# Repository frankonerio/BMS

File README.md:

# Battery Management System (BMS) Project

## Overview
This project has been developed using the following software and libraries:

- **ROS 2**
- **libmodbus** - [Official Website](https://libmodbus.org/)
- **STM32CubeIDE v1.15.1**
- **Segger SystemView Software (PC)** - [Download](https://www.segger.com/products/development-tools/systemview/)
- **Segger SystemView Target Source Files v3.20 (Target Board)**
- **FreeRTOS** - Real-time operating system
- **Wiznet W5500 ioLibrary_BSD** - [Documentation](https://docs.wiznet.io/Product/iEthernet/W5500/driver)

**Author:** fokonkwo@mail.upb.de  
**Date:** 15.01.2025  

---

## 1. BMS Directory Structure

```
├── bms
│   ├── bms.ioc
│   ├── Core
│   │   ├── Inc
│   │   │   ├── BQ769x2Header.h
│   │   │   ├── modbus.h
│   │   │   ├── soc.h
│   │   │   ├── spi.h
│   │   │   ├── FreeRTOSConfig.h    // FreeRTOS configuration or customization file
│   │   ├── Src
│   │   │   ├── main.c
│   │   │   ├── modbus.c    // Modbus battery management system --> host robot communication functions
│   │   │   ├── soc.c    // State estimation functions Coulomb counting and extended Kalman filter functions
│   │   │   ├── utils.c
│   │   ├── Startup
│   │   │   └── startup_stm32f446retx.s
│   ├── Drivers
│   │   ├── CMSIS
│   │   ├── STM32F4xx_HAL_Driver
│   ├── ThirdParty
│   │   ├── FreeRTOS-Kernel
│   │   ├── SEGGER    // For task execution trace capture and debugging real time systems
├── bms_gui
│   ├── include
│   │   └── bms_gui
│   │       ├── mainwindow.h
│   │       └── ros2comm.h  
│   ├── src
│   │   ├── main.cpp
│   │   ├── mainwindow.cpp
│   │   └── ros2comm.cpp    / ROS 2 host node for bms--> host communication and gui interface update
├── FreeRTOS11_with_SystemView.pdf
├── qt_gui
│   ├── main.cpp
│   ├── mainwindow.cpp
│   ├── mainwindow.h
│   ├── mainwindow.ui
└── README.md
```

---

## 2. Getting Started

1. Clone or download and unzip the folder.
2. Run `git submodule init && git submodule update` to initialize and update the FreeRTOS submodule.
3. Open **STM32CubeIDE** and import the project into your workspace.
4. Build the project.
   - If the build fails, ensure all paths are correctly set up.
   - Check project configurations and resolve any missing dependencies.

---

## 3. Integrating FreeRTOS

- Manually added FreeRTOS as a submodule.
- To include FreeRTOS in the STM32CubeIDE project:
  - Create a `ThirdParty` directory and include the FreeRTOS kernel.
  - Include these compiler paths:
    ```
    "${workspace_loc:/${ProjName}/ThirdParty/FreeRTOS-Kernel/include}"
    "${workspace_loc:/${ProjName}/ThirdParty/FreeRTOS-Kernel/portable/GCC/ARM_CM4F}"
    ```
- Ensure `sysmem.c` is **excluded** from the build.

---

## 4. Integrating SEGGER SystemView

- Download **Segger SystemView** for PC and target source files.
- Extract source files into `ThirdParty/SEGGER`.
- Modify **FreeRTOSConfig.h** to include:
  ```c
  #include "SEGGER_SYSVIEW_FreeRTOS.h"
  #define INCLUDE_xTaskGetIdleTaskHandle 1
  #define INCLUDE_pxTaskGetStackStart 1
  ```
- Configure SystemView buffer size and enable **DWT_CYCCNT** register for timestamping.
- Include these compiler paths:
  ```
  "${workspace_loc:/${ProjName}/ThirdParty/SEGGER/Config}"
  "${workspace_loc:/${ProjName}/ThirdParty/SEGGER/SEGGER}"
  "${workspace_loc:/${ProjName}/ThirdParty/SEGGER/OS}"
  ```

---

## 5. Integrating W5500 Ethernet Library

- Download and include the **Wiznet W5500 ioLibrary**.
- Edit `wizchip_conf.h`:
  ```c
  #define _WIZCHIP_ W5500
  ```

---

## 6. ROS 2 Host Node and BMS GUI

- **Build the ROS 2 node** using `colcon build`.
- To modify the GUI:
  - Open `qt_gui` in **Qt Creator**.
  - Edit `mainwindow.ui` as needed.
  - Rebuild the ROS 2 node.

---
## 7. Hardware

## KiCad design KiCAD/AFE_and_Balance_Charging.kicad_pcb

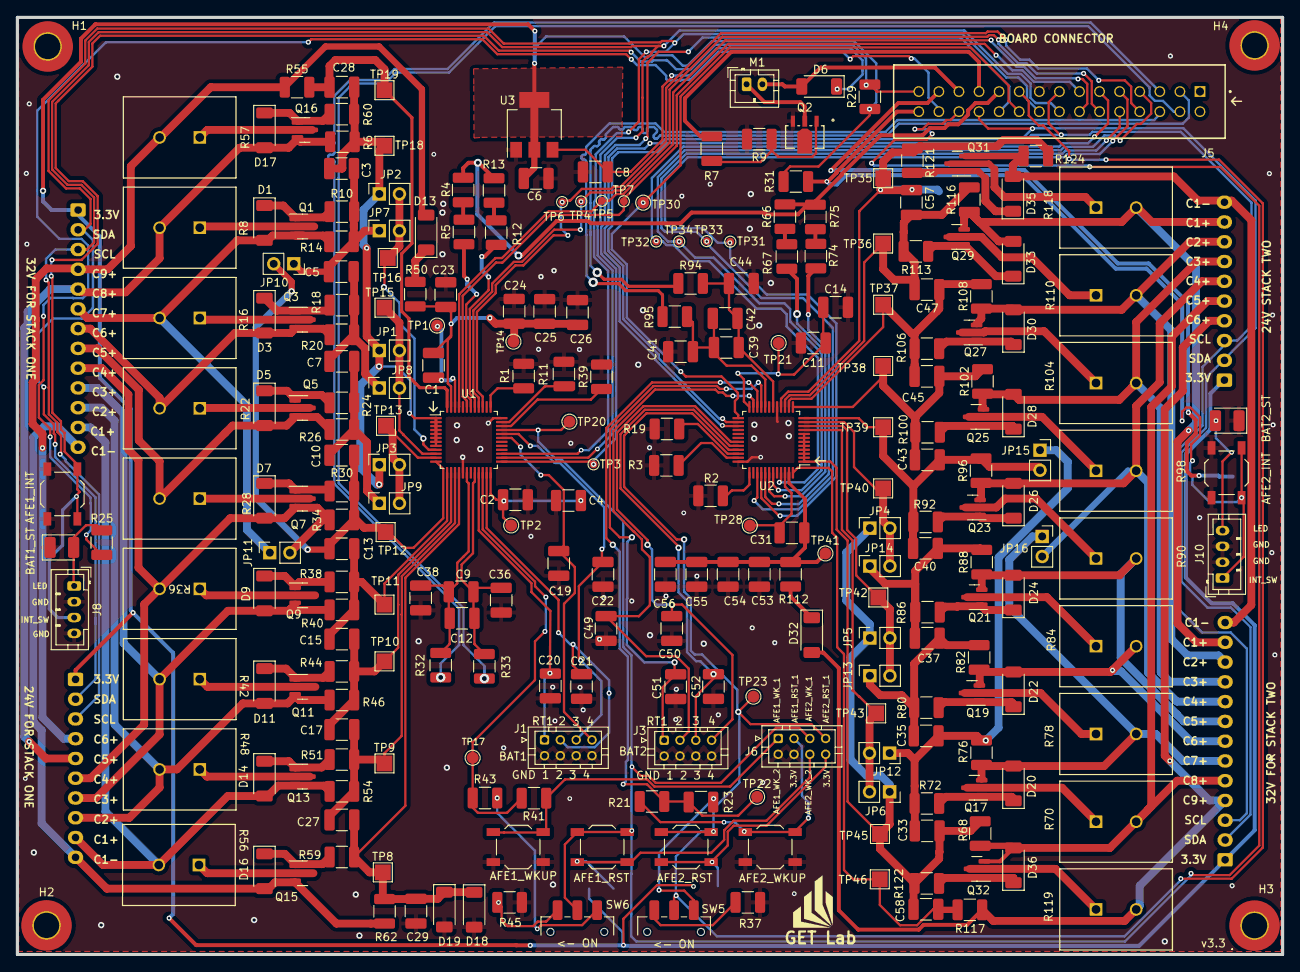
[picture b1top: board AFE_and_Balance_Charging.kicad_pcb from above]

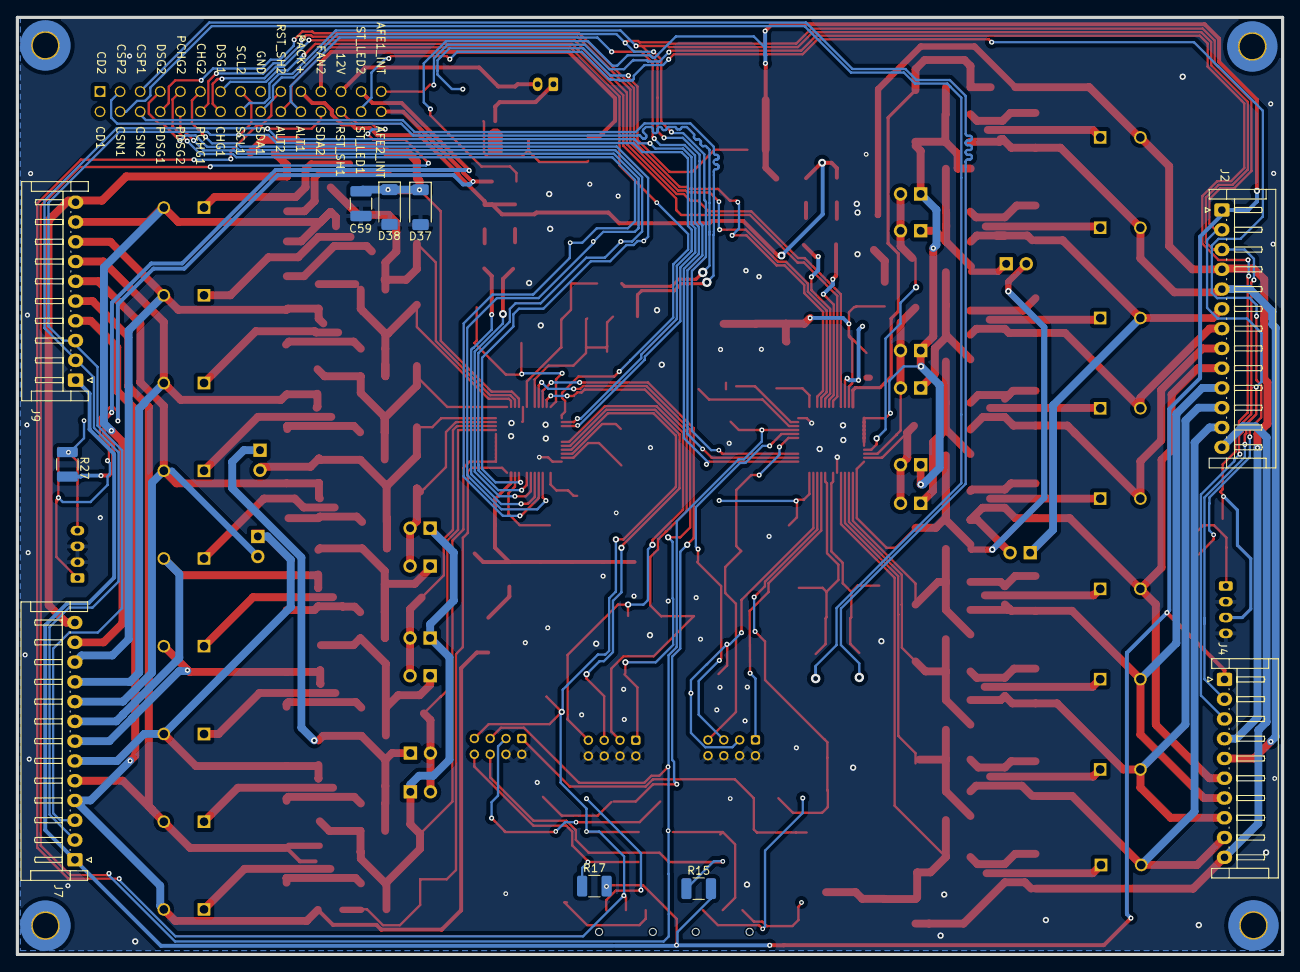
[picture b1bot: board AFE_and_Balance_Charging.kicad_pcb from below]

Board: 2 copper layers, 160.0 x 118.5 mm, 270 parts (10 on the bottom side), 160 nets.

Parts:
C1, C23, C24, C25, C31, C53, C54, C55: 1µF; C_1210_3225Metric_Pad1.33x2.70mm_HandSolder
C2, C11: 2.2µF; C_1210_3225Metric_Pad1.33x2.70mm_HandSolder
C3, C5, C7, C10, C13, C15, C17, C27, C28, C29, C33, C35, C37, C40, C43, C45, C47, C57, C58, C59: 220nF; C_1210_3225Metric_Pad1.33x2.70mm_HandSolder
C4, C14: 0.1uF; C_1210_3225Metric_Pad1.33x2.70mm_HandSolder
C6, C8: 47µF; C_1210_3225Metric_Pad1.33x2.70mm_HandSolder
C9, C19, C20, C21, C22, C26, C39, C49, C50, C51, C52, C56: 100pF; C_1210_3225Metric_Pad1.33x2.70mm_HandSolder
C12, C36, C38, C41, C42, C44: 100nF; C_1210_3225Metric_Pad1.33x2.70mm_HandSolder
D1, D3, D5, D7, D9, D11, D14, D16, D17, D20, D22, D24, D26, D28, D30, D33, D35, D36: 15V; D_SOD-128
D2: YELLOW_LED; LED_1210_3225Metric_Pad1.42x2.65mm_HandSolder
D4: BLUE_LED; LED_1210_3225Metric_Pad1.42x2.65mm_HandSolder
D6, D13, D18, D32, D37: 100V; D_SOD-128
D19, D38: 3.6V; D_SOD-128
H1, H2, H3, H4: MountingHole; MountingHole_3.2mm_M3_Pad_TopBottom
J1, J3: Conn_02x04_Counter_Clockwise; JST_PHD_B8B-PHDSS_2x04_P2.00mm_Vertical
J2, J7: Conn_01x13_Pin; JST_EH_S13B-EH_1x13_P2.50mm_Horizontal
J4, J9: Conn_01x09_Pin; JST_EH_S10B-EH_1x10_P2.50mm_Horizontal
J5: TSS-115-02-L-D; SAMTEC_TSS-115-02-L-D
J6: Conn_02x04_Top_Bottom; JST_PHD_B8B-PHDSS_2x04_P2.00mm_Vertical
J8, J10: Conn_02x02_Top_Bottom; JST_PH_B4B-PH-K_1x04_P2.00mm_Vertical
JP1, JP2, JP3, JP4, JP5, JP6, JP7, JP8, JP9, JP10, JP11, JP12, JP13, JP14, JP15, JP16: Jumper_2_Bridged; PinSocket_1x02_P2.54mm_Vertical
M1: Fan; JST_PH_B2B-PH-K_1x02_P2.00mm_Vertical
Q1, Q3, Q5, Q7, Q9, Q11, Q13, Q15, Q16, Q17, Q19, Q21, Q23, Q25, Q27, Q29, Q31, Q32: AO3416; SOT-23
Q2: FCX495TA; FCX493TA_DIO
R1, R2, R3, R11, R15, R17, R19, R29, R31, R39: 100k; R_1210_3225Metric_Pad1.30x2.65mm_HandSolder
R4, R5, R12, R13, R66, R67, R74, R75: 5.1k; R_1210_3225Metric_Pad1.30x2.65mm_HandSolder
R6, R14, R20, R26, R32, R33, R34, R40, R46, R50, R54, R62, R68, R76, R82, R88, R94, R95, R96, R102, R108, R112, R116, R124: 100; R_1210_3225Metric_Pad1.30x2.65mm_HandSolder
R7, R10, R18, R24, R30, R38, R44, R51, R59, R60, R72, R80, R86, R92, R100, R106, R113, R121, R122: 1k; R_1210_3225Metric_Pad1.30x2.65mm_HandSolder
R8, R16, R22, R28, R36, R42, R48, R56, R57, R70, R78, R84, R90, R98, R104, R110, R118, R119: 4.7; RES_SQM500_YAG
R9, R21, R23, R37, R41, R43, R45: 10k; R_1210_3225Metric_Pad1.30x2.65mm_HandSolder
R25, R27: 4.7K; R_1210_3225Metric_Pad1.30x2.65mm_HandSolder
R55, R117: 20; R_1210_3225Metric_Pad1.30x2.65mm_HandSolder
SW1: Interrupt 2; SW_SPST_TL3342
SW2, SW4, SW7, SW8: Wake_up; SW_SPST_TL3342
SW3: Interrupt 1; SW_SPST_TL3342
SW5, SW6: SHTD; SW_SPDT_CK_JS102011SAQN
TP1, TP2, TP14, TP17, TP20, TP21, TP22, TP23, TP28, TP30, TP41: TestPoint; TestPoint_Pad_D1.5mm
TP3, TP4, TP5, TP6, TP7, TP31, TP32, TP33, TP34: TestPoint; TestPoint_Pad_D1.0mm
TP8, TP9, TP10, TP11, TP12, TP13, TP15, TP16, TP18, TP19, TP35, TP36, TP37, TP38, TP39, TP40, TP42, TP43, TP45, TP46: TestPoint; TestPoint_Pad_2.0x2.0mm
U1, U2: BQ76952PFBR; TQFP-48_7x7mm_P0.5mm
U3: AMS1117-3.3; SOT-223-3_TabPin2

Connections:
+3.3V: C6.1, J2.1, J4.1, J7.1, J9.1, R15.2, R17.2, R29.1, R31.1, U3.2 (VO)
+12V: D6.2 (A), J5.25, M1.2 (-)
/AFE1_INT_A: J5.29, J8.3, R29.2, SW3.1
/AFE1_RST_1: J5.26, J6.5, SW6.2 (B), SW7.1, TP20.1, U1.33 (RST_SHUT)
/AFE1_RST_2: J6.6, R15.1, SW7.2
/AFE1_WK_1: J6.1, R41.1, SW2.1
/AFE2_INT_A: J5.30, J10.1, R31.2, SW1.1
/AFE2_RST_1: J5.19, J6.7, SW5.2 (B), SW8.1, TP23.1, U2.33 (RST_SHUT)
/AFE2_RST_2: J6.8, R17.1, SW8.2
/AFE2_WK_1: J6.3, R21.1, SW4.1
/ALERT1: J5.22, TP3.1, U1.25 (ALERT)
/ALERT2: J5.20, TP30.1, U2.25 (ALERT)
/BQ76952_One/BAT_1: C1.1, C23.1, C24.1, C25.1, C26.1, R50.1, TP14.1, U1.47 (BAT)
/BQ76952_One/LD_1: R12.1, U1.41 (LD)
/BQ76952_One/PACK_1: R5.1, U1.42 (PACK)
/BQ76952_One/SRN_1: C9.2, C12.2, C36.2, R33.2, U1.20 (SRN)
/BQ76952_One/SRP_1: C9.1, C12.1, C38.2, R32.2, U1.18 (SRP)
/BQ76952_One/TEMP4_1: C19.1, J1.7, U1.31 (DCHG)
/BQ76952_One/Temp1_1: C20.1, J1.1, U1.21 (TS1)
/BQ76952_One/Temp2_1: C21.1, J1.3, U1.23 (TS3)
/BQ76952_One/Temp3_1: C22.1, J1.5, U1.32 (DDSG)
/BQ76952_One/VC0: C27.2, C29.1, D18.1 (K), D19.1 (K), R59.2, R62.2, TP8.1, U1.16 (VC0)
/BQ76952_One/VC1: C17.2, C27.1, R51.2, R54.2, TP9.1, U1.15 (VC1)
/BQ76952_One/VC2: C15.2, C17.1, R44.2, R46.2, TP10.1, U1.14 (VC2)
/BQ76952_One/VC3: C13.2, C15.1, R38.2, R40.2, TP11.1, U1.13 (VC3)
/BQ76952_One/VC4: C10.2, C13.1, JP10.2 (B), R30.2, R34.2, TP12.1, U1.12 (VC4)
/BQ76952_One/VC5: JP3.2 (B), JP9.2 (B), TP13.1, U1.11 (VC5)
/BQ76952_One/VC6: JP1.2 (B), JP8.2 (B), TP15.1, U1.10 (VC6)
/BQ76952_One/VC7: JP2.2 (B), JP7.2 (B), TP16.1, U1.9 (VC7)
/BQ76952_One/VC15: C3.1, C28.2, JP1.1 (A), JP2.1 (A), JP3.1 (A), R6.2, R60.2, TP18.1, U1.1 (VC15), U1.2 (VC14), U1.3 (VC13), U1.4 (VC12), U1.5 (VC11), U1.6 (VC10), U1.7 (VC9), U1.8 (VC8)
/BQ76952_One/VC16: C28.1, R55.2, TP19.1, U1.48 (VC16)
/BQ76952_One/WAKE_UP_1: R41.2, R43.2, TP17.1, U1.22 (TS2)
/BQ76952_Two/BAT_2: C31.1, C53.1, C54.1, C55.1, C56.1, R112.1, TP41.1, U2.47 (BAT)
/BQ76952_Two/LD_2: R74.1, U2.41 (LD)
/BQ76952_Two/PACK_2: R67.1, U2.42 (PACK)
/BQ76952_Two/SRN_2: C39.2, C41.2, C42.2, R95.2, U2.20 (SRN)
/BQ76952_Two/SRP_2: C39.1, C42.1, C44.2, R94.2, U2.18 (SRP)
/BQ76952_Two/Temp1_2: C51.1, J3.1, U2.21 (TS1)
/BQ76952_Two/Temp2_2: C49.1, J3.3, U2.23 (TS3)
/BQ76952_Two/Temp3_2: C52.1, J3.5, U2.32 (DDSG)
/BQ76952_Two/Temp4_2: C50.1, J3.7, U2.31 (DCHG)
/BQ76952_Two/VCC0: C57.2, C59.1, D37.1 (K), D38.1 (K), R121.2, R124.2, TP35.1, U2.16 (VC0)
/BQ76952_Two/VCC1: C47.2, C57.1, R113.2, R116.2, TP36.1, U2.15 (VC1)
/BQ76952_Two/VCC2: C45.2, C47.1, R106.2, R108.2, TP37.1, U2.14 (VC2)
/BQ76952_Two/VCC3: C43.2, C45.1, R100.2, R102.2, TP38.1, U2.13 (VC3)
/BQ76952_Two/VCC4: C40.2, C43.1, JP15.2 (B), R92.2, R96.2, TP39.1, U2.12 (VC4)
/BQ76952_Two/VCC5: JP4.2 (B), JP14.2 (B), TP40.1, U2.11 (VC5)
/BQ76952_Two/VCC6: JP5.2 (B), JP13.2 (B), TP42.1, U2.10 (VC6)
/BQ76952_Two/VCC7: JP6.2 (B), JP12.2 (B), TP43.1, U2.9 (VC7)
/BQ76952_Two/VCC15: C33.1, C58.2, JP4.1 (A), JP5.1 (A), JP6.1 (A), R68.2, R122.2, TP45.1, U2.1 (VC15), U2.2 (VC14), U2.3 (VC13), U2.4 (VC12), U2.5 (VC11), U2.6 (VC10), U2.7 (VC9), U2.8 (VC8)
/BQ76952_Two/VCC16: C58.1, R117.2, TP46.1, U2.48 (VC16)
/BQ76952_Two/WAKE_UP_2: R21.2, R23.2, TP22.1, U2.22 (TS2)
/C1+: D14.2 (A), J2.12, J4.9, Q13.2 (S), R54.1, R56.2
/C1-: D16.2 (A), J2.13, J4.10, Q15.2 (S), R62.1
/C2+: D11.2 (A), J2.11, J4.8, Q11.2 (S), R46.1, R48.2
/C3+: D9.2 (A), J2.10, J4.7, Q9.2 (S), R40.1, R42.2
/C4+: D7.2 (A), J2.9, J4.6, JP11.2 (B), Q7.2 (S), R34.1, R36.2
/C5+: D5.2 (A), J2.8, Q5.2 (S), R26.1, R28.2
/C5.+: D17.2 (A), J2.5, J4.5, Q16.2 (S), R6.1, R8.2
/C6+: D3.2 (A), J2.7, Q3.2 (S), R20.1, R22.2
/C6.+: D13.2 (A), J2.4, J4.4, R55.1, R57.2
/C7+: D1.2 (A), J2.6, JP11.1 (A), Q1.2 (S), R14.1, R16.2
/CC1+: D33.2 (A), J7.12, J9.9, Q29.2 (S), R116.1, R118.2
/CC1-: D35.2 (A), J7.13, J9.10, Q31.2 (S), R124.1
/CC2+: D30.2 (A), J7.11, J9.8, Q27.2 (S), R108.1, R110.2
/CC3+: D28.2 (A), J7.10, J9.7, Q25.2 (S), R102.1, R104.2
/CC4+: D26.2 (A), J7.9, J9.6, JP16.2 (B), Q23.2 (S), R96.1, R98.2
/CC5+: D24.2 (A), J7.8, Q21.2 (S), R88.1, R90.2
/CC5.+: D36.2 (A), J7.5, J9.5, Q32.2 (S), R68.1, R70.2
/CC6+: D22.2 (A), J7.7, Q19.2 (S), R82.1, R84.2
/CC6.+: D32.2 (A), J7.4, J9.4, R117.1, R119.2
/CC7+: D20.2 (A), J7.6, JP16.1 (A), Q17.2 (S), R76.1, R78.2
/CHG_1: J5.14, TP5.1, U1.45 (CHG)
/CHG_2: J5.11, TP32.1, U2.45 (CHG)
/C_SEN_N1: J5.04, R33.1
/C_SEN_N2: J5.06, R95.1
/C_SEN_P1: J5.05, R32.1
/C_SEN_P2: J5.03, R94.1
/DSG_1: J5.13, TP7.1, U1.43 (DSG)
/DSG_2: J5.07, TP34.1, U2.43 (DSG)
/FAN2: J5.23, R7.1
/I2C1_SCL: J2.3, J4.3, J5.16, U1.26 (SCL)
/I2C1_SDA: J2.2, J4.2, J5.18, U1.27 (SDA)
/I2C2_SCL: J5.15, J7.3, J9.3, U2.26 (SCL)
/I2C2_SDA: J5.24, J7.2, J9.2, U2.27 (SDA)
/PACK+: J5.21, R4.2, R13.2, R66.2, R75.2
/PCHG_1: J5.12, TP4.1, U1.40 (PCHG)
/PCHG_2: J5.09, TP31.1, U2.40 (PCHG)
/PDSG_1: J5.08, TP6.1, U1.39 (PDSG)
/PDSG_2: J5.10, TP33.1, U2.39 (PDSG)
/REG18_1: C2.1, C4.1, TP2.1, U1.24 (REG18)
/REG18_2: C11.1, C14.1, TP21.1, U2.24 (REG18)
/SHTDN: R45.1, SW6.1 (A)
/SHTDN_2: R37.1, SW5.1 (A)
/SHTDP: R43.1, SW6.3 (C)
/SHTDP_2: R23.1, SW5.3 (C)
/ST_LED1: J5.28, R25.1
/ST_LED2: J5.27, R27.1
/ST_LED_1_B: D2.2 (A), J8.1, R25.2
/ST_LED_2_B: D4.2 (A), J10.4, R27.2
GND: C2.2, C4.2, C6.2, C8.2, C11.2, C14.2, C19.2, C20.2, C21.2, C22.2, C23.2, C24.2, C25.2, C26.2, C29.2, C36.1, C38.1, C41.1, C44.1, C49.2, C50.2, C51.2, C52.2, C53.2, C54.2, C55.2, C56.2, C59.2, D2.1 (K), D4.1 (K), D18.2 (A), D19.2 (A), D37.2 (A), D38.2 (A), J1.2, J1.4, J1.6, J1.8, J3.2, J3.4, J3.6, J3.8, J5.17, J6.2, J6.4, J8.2, J8.4, J10.2, J10.3, Q2.3 (E), R1.2, R2.2, R3.2, R9.2, R11.2, R19.2, R37.2, R39.2, R45.2, SW1.2, SW2.2, SW3.2, SW4.2, U1.17 (VSS), U1.36 (REGIN), U2.17 (VSS), U2.36 (REGIN), U3.1 (GND)
unnamed: D1.1 (K), Q1.1 (G), R10.1
unnamed: D3.1 (K), Q3.1 (G), R18.1
unnamed: D5.1 (K), Q5.1 (G), R24.1
unnamed: C8.1, D6.1 (K), U3.3 (VI)
unnamed: D7.1 (K), Q7.1 (G), R30.1
unnamed: D9.1 (K), Q9.1 (G), R38.1
unnamed: D11.1 (K), Q11.1 (G), R44.1
unnamed: D13.1 (K), R50.2
unnamed: D14.1 (K), Q13.1 (G), R51.1
unnamed: D16.1 (K), Q15.1 (G), R59.1
unnamed: D17.1 (K), Q16.1 (G), R60.1
unnamed: D20.1 (K), Q17.1 (G), R72.1
unnamed: D22.1 (K), Q19.1 (G), R80.1
unnamed: D24.1 (K), Q21.1 (G), R86.1
unnamed: D26.1 (K), Q23.1 (G), R92.1
unnamed: D28.1 (K), Q25.1 (G), R100.1
unnamed: D30.1 (K), Q27.1 (G), R106.1
unnamed: D32.1 (K), R112.2
unnamed: D33.1 (K), Q29.1 (G), R113.1
unnamed: D35.1 (K), Q31.1 (G), R121.1
unnamed: D36.1 (K), Q32.1 (G), R122.1
unnamed: C5.2, C7.1, JP8.1 (A), R18.2, R20.2
unnamed: C7.2, C10.1, JP9.1 (A), R24.2, R26.2
unnamed: C3.2, C5.1, JP7.1 (A), JP10.1 (A), R10.2, R14.2
unnamed: C33.2, C35.1, JP12.1 (A), JP15.1 (A), R72.2, R76.2
unnamed: C35.2, C37.1, JP13.1 (A), R80.2, R82.2
unnamed: C37.2, C40.1, JP14.1 (A), R86.2, R88.2
unnamed: M1.1 (+), Q2.2 (C)
unnamed: Q1.3 (D), R8.1
unnamed: Q2.1 (B), R7.2, R9.1
unnamed: Q3.3 (D), R16.1
unnamed: Q5.3 (D), R22.1
unnamed: Q7.3 (D), R28.1
unnamed: Q9.3 (D), R36.1
unnamed: Q11.3 (D), R42.1
unnamed: Q13.3 (D), R48.1
unnamed: Q15.3 (D), R56.1
unnamed: Q16.3 (D), R57.1
unnamed: Q17.3 (D), R70.1
unnamed: Q19.3 (D), R78.1
unnamed: Q21.3 (D), R84.1
unnamed: Q23.3 (D), R90.1
unnamed: Q25.3 (D), R98.1
unnamed: Q27.3 (D), R104.1
unnamed: Q29.3 (D), R110.1
unnamed: Q31.3 (D), R118.1
unnamed: Q32.3 (D), R119.1
unnamed: R4.1, R5.2
unnamed: R12.2, R13.1
unnamed: R66.1, R67.2
unnamed: R74.2, R75.1
unnamed: R1.1, U1.37 (BREG)
unnamed: C1.2, TP1.1, U1.46 (CP1)
unnamed: R11.1, U1.35 (REG1)
unnamed: R39.1, U1.34 (REG2)
unnamed: R2.1, U2.37 (BREG)
unnamed: C31.2, TP28.1, U2.46 (CP1)
unnamed: R3.1, U2.35 (REG1)
unnamed: R19.1, U2.34 (REG2)

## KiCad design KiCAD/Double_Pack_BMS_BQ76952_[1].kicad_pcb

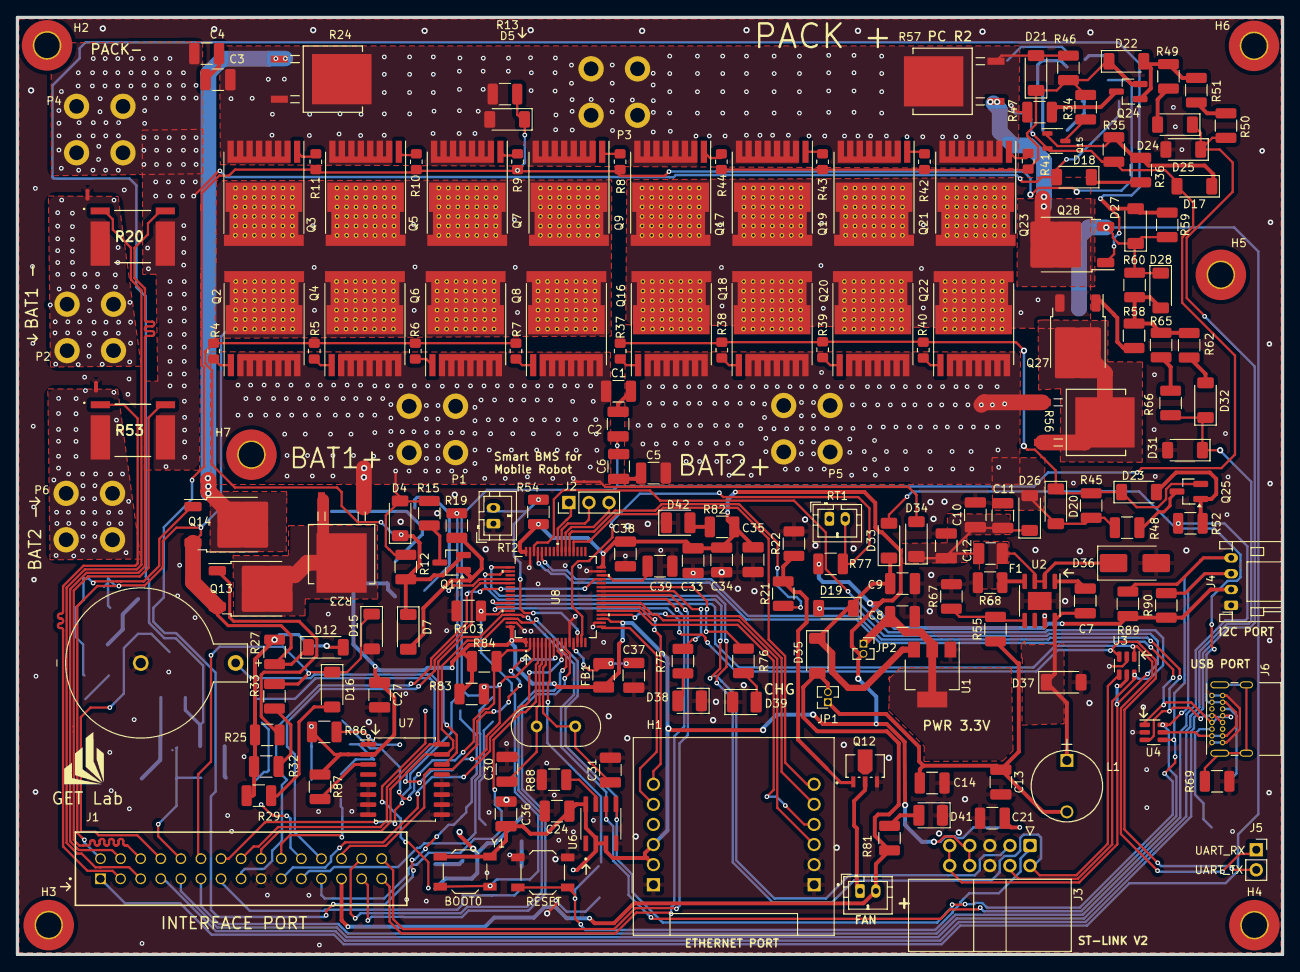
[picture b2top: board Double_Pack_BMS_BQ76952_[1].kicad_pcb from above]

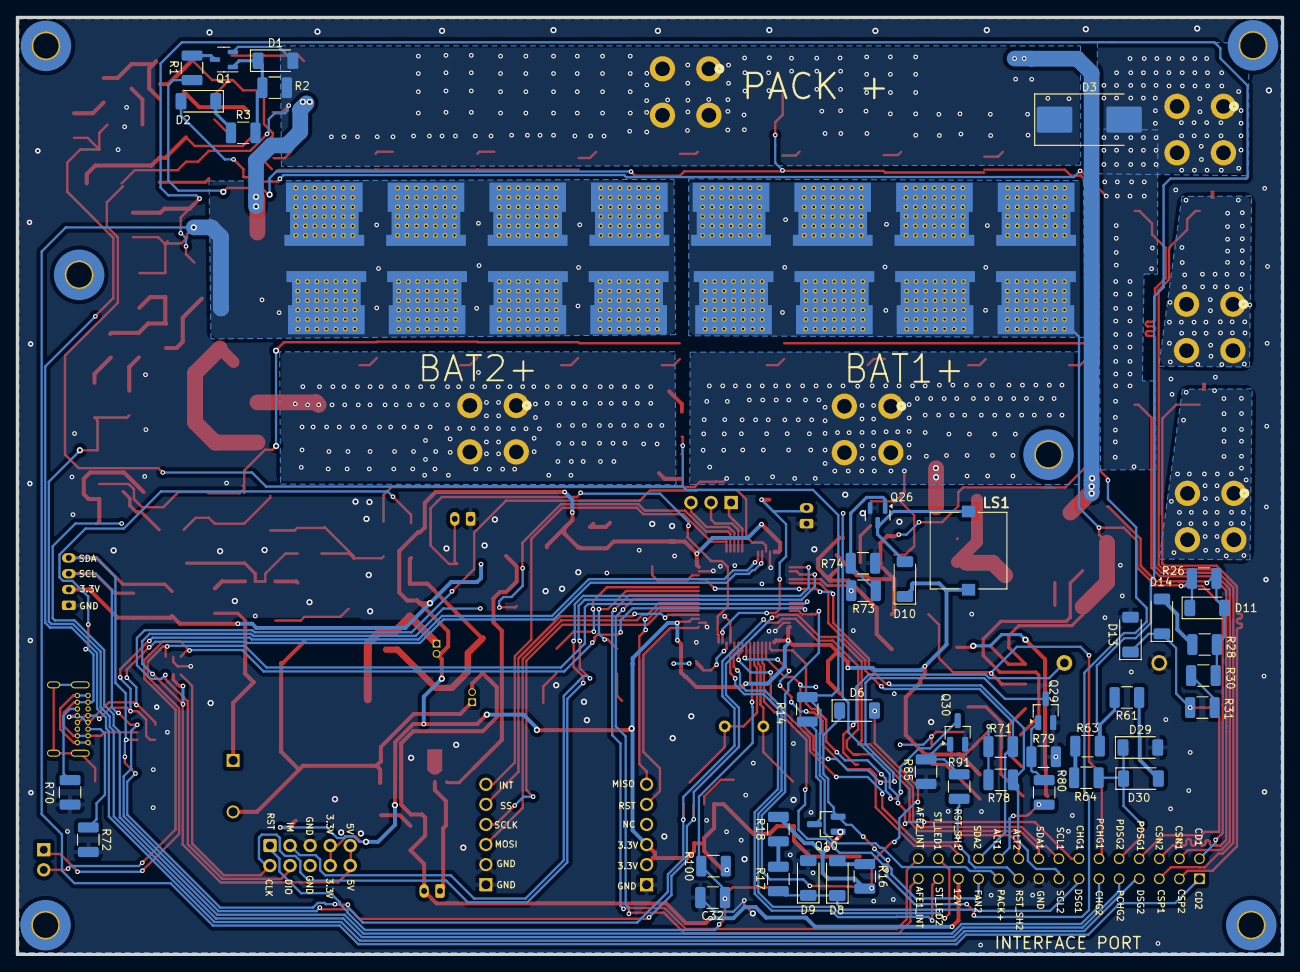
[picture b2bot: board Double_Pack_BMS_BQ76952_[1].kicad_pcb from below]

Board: 2 copper layers, 160.0 x 118.5 mm, 232 parts (44 on the bottom side), 153 nets.

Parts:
BT1: Battery_Cell; BAT_BAT-HLD-011-THM
C1, C2, C3, C4, C5, C6, C7, C12: 100nF; C_1210_3225Metric_Pad1.33x2.70mm_HandSolder
C8, C9, C13, C14: 47µF; C_1210_3225Metric_Pad1.33x2.70mm_HandSolder
C10, C11: 2.2µF; C_1210_3225Metric_Pad1.33x2.70mm_HandSolder
C21, C24, C27, C33, C34: 4.7uF; C_1210_3225Metric_Pad1.33x2.70mm_HandSolder
C30, C31: 30pF; C_1210_3225Metric_Pad1.33x2.70mm_HandSolder
C32, C35, C36, C37: 0.1uF; C_1210_3225Metric_Pad1.33x2.70mm_HandSolder
C38, C39: 2.2uF; C_1210_3225Metric_Pad1.33x2.70mm_HandSolder
D1, D4, D5, D11, D12, D17, D20, D21, D27, D28: 16V; D_SOD-128
D2, D6, D7, D8, D9, D13, D14, D15, D16, D18, D19, D22, D23, D24, D25, D26, D29, D30, D31, D32, D33, D34, D35, D37: 100V; D_SOD-128
D3: SMCJ60A; D_SMC_Handsoldering
D10: UF4007; D_SOD-128
D36: 60V; D_SMB_Handsoldering
D38, D42: GREEN_LED; LED_1210_3225Metric_Pad1.42x2.65mm_HandSolder
D39, D41: RED_LED; LED_1210_3225Metric_Pad1.42x2.65mm_HandSolder
F1: Fuse; L_1210_3225Metric_Pad1.42x2.65mm_HandSolder
FB1: FerriteBead; L_1210_3225Metric_Pad1.42x2.65mm_HandSolder
H1: WIZ850IO
H2, H3, H4, H5, H6, H7: MountingHole; MountingHole_3.2mm_M3_Pad_TopBottom
J1: TSS-115-02-L-D; SAMTEC_TSS-115-02-L-D
J2: Conn_01x04_Pin; PinHeader_1x03_P2.54mm_Vertical
J3: Conn_02x05_Odd_Even; IDC-Header_2x05_P2.54mm_Horizontal
J4: Conn_01x04; JST_PH_S4B-PH-K_1x04_P2.00mm_Horizontal
J5: Conn_01x02_Pin; PinSocket_1x02_P2.54mm_Vertical
J6: USB_C_Receptacle_USB2.0_16P; USB_C_Receptacle_GCT_USB4085
JP1, JP2: Jumper_2_Bridged; PinSocket_1x02_P1.27mm_Vertical
L1: 10µH; Inductor_10uH_THT
LS1: CMI-9705-0380-SMT-TR; CMI97050380SMTTR
M1: Fan; JST_PH_B2B-PH-K_1x02_P2.00mm_Vertical
NT1, NT2: NetTie; NetTie-2_SMD_Pad0.5mm
P1, P2, P3, P4, P5, P6: 74651174R; CONN4_74651174R_WRE
Q1, Q15: BSS123N; SOT-23-3
Q2, Q3, Q4, Q5, Q6, Q7, Q8, Q9, Q16, Q17, Q18, Q19, Q20, Q21, Q22, Q23: IPT015N10N5; Infineon_PG-HSOF-8-1_ThermalVias
Q10, Q11, Q24, Q25: MMBT5401-7-F; SOT-23_Handsoldering
Q12: FCX495TA; FCX493TA_DIO
Q13, Q14, Q27, Q28: IRFR6215TRLPBF; TO-252-2
Q26: BC818; SOT-23
Q29, Q30: BC818; SOT-23_Handsoldering
R1, R14, R15, R34, R47, R48: 100R; R_1210_3225Metric_Pad1.30x2.65mm_HandSolder
R2, R12, R13, R26, R27, R35, R45, R46, R59, R60: 10M; R_1210_3225Metric_Pad1.30x2.65mm_HandSolder
R3, R22, R36, R54, R67, R74, R77, R79, R85, R88, R100, R103: 10k; R_1210_3225Metric_Pad1.30x2.65mm_HandSolder
R4, R5, R6, R7, R8, R9, R10, R11, R37, R38, R39, R40, R41, R42, R43, R44: 47R; R_0805_2012Metric_Pad1.20x1.40mm_HandSolder
R16, R21, R49: 1k; R_1210_3225Metric_Pad1.30x2.65mm_HandSolder
R17, R18, R19, R28, R29, R30, R31, R32, R33, R50, R51, R52, R61, R62, R63, R64, R65, R66, R70, R72, R80, R91: 5.1k; R_1210_3225Metric_Pad1.30x2.65mm_HandSolder
R20, R53: WSL4026L3000FEA
R23, R24, R56, R57: 40; RES_PWR163_BRN-L
R25, R58: 47R; R_1210_3225Metric_Pad1.30x2.65mm_HandSolder
R55: 150k; R_1210_3225Metric_Pad1.30x2.65mm_HandSolder
R68: 49.9k; R_1210_3225Metric_Pad1.30x2.65mm_HandSolder
R69: 1M; R_1210_3225Metric_Pad1.30x2.65mm_HandSolder
R71, R78, R89, R90: 4.7k; R_1210_3225Metric_Pad1.30x2.65mm_HandSolder
R73: 2.2K; R_1210_3225Metric_Pad1.30x2.65mm_HandSolder
R75, R76, R82: 4.7K; R_1210_3225Metric_Pad1.30x2.65mm_HandSolder
R81: 10K; R_1210_3225Metric_Pad1.30x2.65mm_HandSolder
R83, R84: 100k; R_1210_3225Metric_Pad1.30x2.65mm_HandSolder
R86, R87: 2.2k; R_1210_3225Metric_Pad1.30x2.65mm_HandSolder
RT1, RT2: 10k; JST_PH_B2B-PH-K_1x02_P2.00mm_Vertical
SW1, SW2: BOOT; SW_SPST_TL3342
U1: AMS1117-3.3; SOT-223-3_TabPin2
U2: LMR16030; SOIC-8-1EP_3.9x4.9mm_P1.27mm_EP2.29x3mm
U3, U4: SRV05-4; SOT-23-6
U6: M24M01-RMN6TP; M24M01-RMN6TP_SOIC127P600X175-8N
U7: DS3231M; SOIC-16W_7.5x10.3mm_P1.27mm
U8: STM32F446RET6; LQFP64-10x10mm
Y1: 16MHZ; Crystal_HC49-U_Vertical

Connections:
+3.3V: C21.1, C24.1, C27.1, C33.1, C34.1, C35.1, C36.1, C38.1, D10.1 (K), FB1.1, H1.8 (3.3V_1), H1.9 (3.3V_2), J3.7, J3.8, J4.2, JP2.2 (B), LS1.1 (+), R54.2, R71.1, R77.2, R78.1, R82.1, R83.1, R84.1, R86.1, R87.1, R89.1, R90.1, R100.1, SW1.1, U6.2 (E1), U6.3 (E2), U6.8 (VCC), U7.2 (VCC), U8.1 (VBAT), U8.19 (VDD), U8.32 (VDD), U8.48 (VDD), U8.64 (VDD)
+12V: D35.2 (A), J1.25, JP1.2 (B), M1.2 (-), R81.1
/AFE1_Interrupt: J1.29, U8.24 (PC4)
/AFE2_Interrupt: J1.30, U8.25 (PC5)
/ALERT1: J1.22, R80.1
/ALERT2: J1.20, R91.1
/BAT-: NT1.1, P2.1, P2.2, P2.3, P2.4, R20.2
/BAT_2+: C5.1, D20.2 (A), D26.2 (A), P5.1, P5.2, P5.3, P5.4, Q16.2 (S), Q18.2 (S), Q20.2 (S), Q22.2 (S), R45.2, R48.1, R56.1
/CDSGTempSensor: R54.1, RT2.2, U8.14 (PA0)
/CDSGTempSensor_2: R77.1, RT1.2, U8.15 (PA1)
/CHG_1: J1.14, R19.1
/CHG_2: J1.11, R52.1
/C_SEN_N1: J1.04, R20.4
/C_SEN_N2: J1.06, R53.4
/C_SEN_P1: J1.05, R20.1
/C_SEN_P2: J1.03, R53.1
/DSG_1: D8.1 (K), D9.1 (K), J1.13, R17.1
/DSG_1-: D11.1 (K), D12.1 (K), J1.02, Q2.3 (D), Q3.3 (D), Q4.3 (D), Q5.3 (D), Q6.3 (D), Q7.3 (D), Q8.3 (D), Q9.3 (D), Q13.3 (S), Q14.3 (D), R26.2, R27.1
/DSG_2: D24.1 (K), D25.1 (K), J1.07, R50.1
/DSG_2-: D27.1 (K), D28.1 (K), J1.01, Q16.3 (D), Q17.3 (D), Q18.3 (D), Q19.3 (D), Q20.3 (D), Q21.3 (D), Q22.3 (D), Q23.3 (D), Q27.3 (D), Q28.3 (D), R59.2, R60.1
/FAN1: R21.1, U8.37 (PC6)
/FAN2: J1.23, U8.4 (PC15-OSC32_OUT)
/I2C1_SCL: J1.16, J4.3, R90.2, U4.6 (IO4), U6.6 (SCL), U7.16 (SCL), U8.61 (PB8)
/I2C1_SDA: J1.18, J4.4, R89.2, U4.4 (IO3), U6.5 (SDA), U7.15 (SDA), U8.62 (PB9)
/I2C2_SDA: J1.24, R71.2, U8.53 (PC12)
/I2C2_SDL: J1.15, R78.2, U8.29 (PB10)
/INTERCOMM/COM_DM: J6.A7 (D-), J6.B7 (D-), U4.3 (IO2), U8.44 (PA11)
/INTERCOMM/COM_DP: J6.A6 (D+), J6.B6 (D+), U4.1 (IO1), U8.45 (PA12)
/INTERCOMM/COM_RXD: J5.1, U3.1 (IO1), U8.58 (PB6)
/INTERCOMM/COM_TXD: J5.2, U3.3 (IO2), U8.59 (PB7)
/INTERCOMM/SPI_INT: H1.6 (INTN), U8.36 (PB15)
/INTERCOMM/SPI_MISO: H1.12 (MISO), U8.22 (PA6)
/INTERCOMM/SPI_MOSI: H1.3 (MOSI), U8.23 (PA7)
/INTERCOMM/SPI_RST: H1.11 (RSTN), U8.17 (PA3)
/INTERCOMM/SPI_SCK: H1.4 (SCLK), U8.21 (PA5)
/INTERCOMM/SPI_SS: H1.5 (SCNN), U8.20 (PA4)
/INTERCOMM/SWCLK: J3.2, U3.4 (IO3), U8.49 (PA14)
/INTERCOMM/SWDIM: J3.3, U8.50 (PA15)
/INTERCOMM/SWDIO: J3.4, U3.6 (IO4), U8.46 (PA13)
/INTERCOMM/SWRST: C32.1, J3.1, R100.2, SW2.2, U8.7 (NRST)
/INTERCOMM/SW_5V: D19.2 (A), J3.9, J3.10, U3.5 (VP)
/INTERCOMM/VBUS: D33.2 (A), J6.A4 (VBUS), J6.A9 (VBUS), J6.B4 (VBUS), J6.B9 (VBUS), U4.5 (VP)
/MOSFET_Array_One/BAT+: C1.1, D4.2 (A), D34.2 (A), P1.1, P1.2, P1.3, P1.4, Q2.2 (S), Q4.2 (S), Q6.2 (S), Q8.2 (S), R12.2, R15.1, R23.1
/MOSFET_Array_One/DSG1_Gate: D5.1 (K), D6.1 (K), Q10.2 (E), R1.1, R8.2, R9.2, R10.2, R11.2, R13.1
/MOSFET_Array_One/PRE_IN: Q13.2 (D), R23.2, R23.3
/MOSFET_Array_One/PRE_OUT: Q14.2 (S), R24.1
/MOSFET_Array_Two/BAT_2-: NT2.1, P6.1, P6.2, P6.3, P6.4, R53.2
/MOSFET_Array_Two/DSG2_Gate: D21.1 (K), D22.1 (K), Q24.2 (E), R34.1, R41.2, R42.2, R43.2, R44.2, R46.1
/MOSFET_Array_Two/PRE_IN_2: Q27.2 (S), R56.2, R56.3
/MOSFET_Array_Two/PRE_OUT_2: Q28.2 (S), R57.1
/PACK+: C2.2, C3.1, C6.2, D1.2 (A), D3.1 (K), D5.2 (A), D17.2 (A), D21.2 (A), J1.21, P3.1, P3.2, P3.3, P3.4, Q1.2 (S), Q3.2 (S), Q5.2 (S), Q7.2 (S), Q9.2 (S), Q15.2 (S), Q17.2 (S), Q19.2 (S), Q21.2 (S), Q23.2 (S), R2.2, R13.2, R14.1, R24.2, R24.3, R35.2, R46.2, R47.1, R57.2, R57.3
/PACK-: C4.2, D2.2 (A), D3.2 (A), D18.2 (A), P4.1, P4.2, P4.3, P4.4, R20.3, R53.3
/PCHG_1: D15.1 (K), D16.1 (K), J1.12, R33.1
/PCHG_2: D31.1 (K), D32.1 (K), J1.09, R66.1
/PDSG_1: D13.1 (K), D14.1 (K), J1.08, R31.1
/PDSG_2: D29.1 (K), D30.1 (K), J1.10, R64.1
/Power_Supply/3.3V_out: C8.1, JP2.1 (A), U1.2 (VO)
/Power_Supply/12V_Out: C13.1, C14.1, JP1.1 (A), L1.2, R55.1
/Power_Supply/FB: R55.2, R67.1, U2.5 (FB)
/Power_Supply/SW: C7.2, D37.1 (K), L1.1, U2.8 (SW)
/Power_Supply/VIN: D36.1 (K), F1.2, U2.2 (VIN), U2.3 (EN)
/Power_Supply/VIN_INPUT: C10.1, C11.1, C12.1, D26.1 (K), D34.1 (K), F1.1
/RST_SHUT_1: J1.26, U8.8 (PC0)
/RST_SHUT_2: J1.19, U8.9 (PC1)
/STM32F446RET6/BOOT0: R103.1, SW1.2, U8.60 (BOOT0)
/STM32F446RET6/BUZZER: R73.2, U8.52 (PC11)
/STM32F446RET6/CHG_LED: R76.1, U8.27 (PB1)
/STM32F446RET6/DCHG_LED: R75.1, U8.26 (PB0)
/STM32F446RET6/OSC_IN: C30.1, U8.5 (PH0-OSC_IN), Y1.1
/STM32F446RET6/OSC_OUT: C31.1, U8.6 (PH1), Y1.2
/STM32F446RET6/PC7: J2.3, U8.38 (PC7)
/STM32F446RET6/PC8: J2.2, U8.39 (PC8)
/STM32F446RET6/PC9: J2.1, U8.40 (PC9)
/STM32F446RET6/VCAP_1: C39.1, U8.30 (VCAP_1)
/STM_ALERT1: Q29.3 (C), R83.2, U8.3 (PC14-OSC32_IN)
/STM_ALERT2: Q30.3 (C), R84.2, U8.2 (PC13)
/ST_LED1: J1.28, U8.10 (PC2)
/ST_LED2: J1.27, U8.11 (PC3)
GND: BT1.2 (-), C8.2, C9.2, C10.2, C11.2, C12.2, C13.2, C14.2, C21.2, C24.2, C27.2, C30.2, C31.2, C32.2, C33.2, C34.2, C35.2, C36.2, C37.2, C38.2, C39.2, D9.2 (A), D13.2 (A), D15.2 (A), D25.2 (A), D29.2 (A), D31.2 (A), D36.2 (A), D37.2 (A), D38.1 (K), D39.1 (K), D41.1 (K), D42.1 (K), H1.1 (GND_1), H1.2 (GND_2), H1.7 (GND_3), J1.17, J3.5, J3.6, J4.1, J6.A1 (GND), J6.A12 (GND), J6.B1 (GND), J6.B12 (GND), NT1.2, NT2.2, Q12.3 (E), Q26.2 (E), Q29.2 (E), Q30.2 (E), R22.2, R67.2, R68.2, R69.2, R70.2, R72.2, R74.2, R79.2, R85.2, R88.2, R103.2, RT1.1, RT2.1, SW2.1, U1.1 (GND), U2.7 (GND), U2.9 (PAD), U3.2 (VN), U4.2 (VN), U6.4 (VSS), U7.5 (GND), U7.6 (GND), U7.7 (GND), U7.8 (GND), U7.9 (GND), U7.10 (GND), U7.11 (GND), U7.12 (GND), U7.13 (GND), U8.12 (VSSA/VREF-), U8.18 (VSS), U8.31 (VSS), U8.47 (VSS), U8.63 (VSS)
unnamed: BT1.1 (+), U7.14 (VBAT)
unnamed: C1.2, C2.1
unnamed: C3.2, C4.1
unnamed: C5.2, C6.1
unnamed: D1.1 (K), Q1.1 (G), R2.1, R3.2
unnamed: D2.1 (K), R3.1
unnamed: D4.1 (K), D7.1 (K), Q11.2 (E), R4.2, R5.2, R6.2, R7.2, R12.1
unnamed: D6.2 (A), Q10.1 (B), R16.2, R18.2
unnamed: D7.2 (A), Q11.1 (B), R19.2
unnamed: D8.2 (A), R16.1
unnamed: D10.2 (A), LS1.2 (-), Q26.3 (C)
unnamed: D11.2 (A), Q14.1 (G), R26.1, R28.2, R30.2
unnamed: D12.2 (A), R25.2, R27.2, R29.2, R32.2
unnamed: D14.2 (A), R28.1
unnamed: D16.2 (A), R29.1
unnamed: D17.1 (K), Q15.1 (G), R35.1, R36.2
unnamed: D18.1 (K), R36.1
unnamed: C9.1, D19.1 (K), D33.1 (K), D35.1 (K), U1.3 (VI)
unnamed: D20.1 (K), D23.1 (K), Q25.2 (E), R37.2, R38.2, R39.2, R40.2, R45.1
unnamed: D22.2 (A), Q24.1 (B), R49.2, R51.2
unnamed: D23.2 (A), Q25.1 (B), R52.2
unnamed: D24.2 (A), R49.1
unnamed: D27.2 (A), Q28.1 (G), R59.1, R61.2, R63.2
unnamed: D28.2 (A), R58.2, R60.2, R62.2, R65.2
unnamed: D30.2 (A), R61.1
unnamed: D32.2 (A), R62.1
unnamed: D38.2 (A), R75.2
unnamed: D39.2 (A), R76.2
unnamed: D41.2 (A), R81.2
unnamed: D42.2 (A), R82.2
unnamed: J6.A5 (CC1), R72.1
unnamed: J6.B5 (CC2), R70.1
unnamed: J6.S1 (SHIELD), R69.1
unnamed: M1.1 (+), Q12.2 (C)
unnamed: Q1.3 (D), R1.2
unnamed: Q2.1 (G), R4.1
unnamed: Q3.1 (G), R11.1
unnamed: Q4.1 (G), R5.1
unnamed: Q5.1 (G), R10.1
unnamed: Q6.1 (G), R6.1
unnamed: Q7.1 (G), R9.1
unnamed: Q8.1 (G), R7.1
unnamed: Q9.1 (G), R8.1
unnamed: Q10.3 (C), R14.2
unnamed: Q11.3 (C), R15.2
unnamed: Q12.1 (B), R21.2, R22.1
unnamed: Q13.1 (G), R25.1
unnamed: Q15.3 (D), R34.2
unnamed: Q16.1 (G), R37.1
unnamed: Q17.1 (G), R44.1
unnamed: Q18.1 (G), R38.1
unnamed: Q19.1 (G), R43.1
unnamed: Q20.1 (G), R39.1
unnamed: Q21.1 (G), R42.1
unnamed: Q22.1 (G), R40.1
unnamed: Q23.1 (G), R41.1
unnamed: Q24.3 (C), R47.2
unnamed: Q25.3 (C), R48.2
unnamed: Q26.1 (B), R73.1, R74.1
unnamed: Q27.1 (G), R58.1
unnamed: Q29.1 (B), R79.1, R80.2
unnamed: Q30.1 (B), R85.1, R91.2
unnamed: R17.2, R18.1
unnamed: R30.1, R31.2
unnamed: R32.1, R33.2
unnamed: R50.2, R51.1
unnamed: R63.1, R64.2
unnamed: R65.1, R66.2
unnamed: C7.1, U2.1 (BOOT)
unnamed: R68.1, U2.4 (RT_SYNC)
unnamed: R88.1, U6.7 (*WC)
unnamed: R86.2, U7.1 (32KHZ)
unnamed: R87.2, U7.3 (~INT/SQW)
VDD: C37.1, FB1.2, U8.13 (VDDA/VREF+)

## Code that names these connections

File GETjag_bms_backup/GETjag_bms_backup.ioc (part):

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Mcu.Name=STM32F446R(C-E)Tx
Mcu.Package=LQFP64
Mcu.UserName=STM32F446RETx
PA13.Signal=SYS_JTMS-SWDIO
PA14.GPIOParameters=GPIO_Label
PA14.GPIO_Label=TCK
PA14.Signal=SYS_JTCK-SWCLK
PA2.Mode=Half_duplex(single_wire_mode)
PA2.Signal=USART2_TX
PA3.GPIOParameters=GPIO_Label
PA3.GPIO_Label=GPIO_W5500_RESET
PA3.Signal=GPIO_Output
PA4.GPIOParameters=GPIO_Label
PA4.GPIO_Label=GPIO_W5500_CS
PA4.Signal=GPIO_Output
PA5.Mode=Full_Duplex_Master
PA5.Signal=SPI1_SCK
PA6.Mode=Full_Duplex_Master
PA6.Signal=SPI1_MISO
PA7.Mode=Full_Duplex_Master
PA7.Signal=SPI1_MOSI
PB0.GPIOParameters=GPIO_Label
PB0.GPIO_Label=LED_1
PB0.Signal=GPIO_Output
PB1.GPIOParameters=GPIO_Label
PB1.GPIO_Label=LED_2
PB1.Signal=GPIO_Output
PB15.GPIOParameters=GPIO_Label
PB15.GPIO_Label=SPI_INT
PB15.Signal=GPIO_Output
PB6.Mode=Asynchronous
PB6.Signal=USART1_TX
PB7.Mode=Asynchronous
PB7.Signal=USART1_RX
PB8.Mode=I2C
PB8.Signal=I2C1_SCL
PB9.Mode=I2C
PB9.Signal=I2C1_SDA
PC11.GPIOParameters=GPIO_PuPd,GPIO_Label
PC11.GPIO_Label=BUZZER
PC11.GPIO_PuPd=GPIO_NOPULL
PC11.Signal=GPIO_Output
PC7.GPIOParameters=GPIO_PuPd,GPIO_Label
PC7.GPIO_Label=BQ_RESET
PC7.GPIO_PuPd=GPIO_PULLDOWN
PC7.Signal=GPIO_Output
PH0-OSC_IN.Mode=HSE-External-Oscillator
PH0-OSC_IN.Signal=RCC_OSC_IN
PH1-OSC_OUT.Mode=HSE-External-Oscillator
PH1-OSC_OUT.Signal=RCC_OSC_OUT
RCC.HSE_VALUE=16000000
RCC.SYSCLKFreq_VALUE=168000000
RCC.SYSCLKSource=RCC_SYSCLKSOURCE_PLLCLK
board=NUCLEO-F446RE
boardIOC=true

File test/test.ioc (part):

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Mcu.Name=STM32F446R(C-E)Tx
Mcu.Package=LQFP64
Mcu.UserName=STM32F446RETx
PA11.Mode=Device_Only
PA11.Signal=USB_OTG_FS_DM
PA12.Mode=Device_Only
PA12.Signal=USB_OTG_FS_DP
PA13.Signal=SYS_JTMS-SWDIO
PA14.Signal=SYS_JTCK-SWCLK
PB0.GPIOParameters=GPIO_PuPd,GPIO_Label
PB0.GPIO_Label=LED
PB0.GPIO_PuPd=GPIO_PULLUP
PB0.Signal=GPIO_Output
PB1.GPIOParameters=GPIO_Label
PB1.GPIO_Label=LED_2
PB1.Signal=GPIO_Output
PB8.Mode=I2C
PB8.Signal=I2C1_SCL
PB9.Mode=I2C
PB9.Signal=I2C1_SDA
PC0.GPIOParameters=GPIO_Label
PC0.GPIO_Label=DFETOFF
PC0.Signal=GPIO_Output
PC1.GPIOParameters=GPIO_PuPd,GPIO_Label
PC1.GPIO_Label=CFETOFF
PC1.GPIO_PuPd=GPIO_PULLDOWN
PC1.Signal=GPIO_Output
PC11.GPIOParameters=GPIO_Label
PC11.GPIO_Label=BUZZER
PC11.Signal=GPIO_Output
PC13.GPIOParameters=GPIO_PuPd,GPIO_Label
PC13.GPIO_Label=ALERT_PIN_2
PC13.GPIO_PuPd=GPIO_PULLDOWN
PC13.Signal=GPIO_Input
PC14-OSC32_IN.Signal=RCC_OSC32_IN
PC15-OSC32_OUT.Signal=RCC_OSC32_OUT
PC7.GPIOParameters=GPIO_Label
PC7.GPIO_Label=PC7
PC7.Signal=GPIO_Output
PC9.GPIOParameters=GPIO_PuPd,GPIO_Label
PC9.GPIO_Label=RST_SHUT
PC9.GPIO_PuPd=GPIO_PULLDOWN
PC9.Signal=GPIO_Output
PH0-OSC_IN.Mode=HSE-External-Oscillator
PH0-OSC_IN.Signal=RCC_OSC_IN
PH1-OSC_OUT.Mode=HSE-External-Oscillator
PH1-OSC_OUT.Signal=RCC_OSC_OUT
RCC.HSE_VALUE=16000000
RCC.SYSCLKFreq_VALUE=72000000
RCC.SYSCLKSource=RCC_SYSCLKSOURCE_PLLCLK
board=custom

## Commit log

2024-06-03 add FreeRTOS
2024-06-03 test
2024-06-03 add gui-modbus ros2 node
2024-07-18 add protection and test srcs
2024-08-26 set up FreeRTOS tasks
2024-09-16 state_machine_OCD1_fix
2024-09-29 working test 1
2025-03-28 Update README.md to include Hardware
